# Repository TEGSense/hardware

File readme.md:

# TEG Sense Board

This is a thermoelectric generator (TEG) boost converter used to power a connected battery or capacitor to periodically operate a microcontroller reading from a biometric sensor to compute blood oxygen saturation. That was a big sentence!

This is the board version used in the published paper, revision 3 of the rigid prototypes.
It is used in conjunction with the [SpO2 board](https://github.com/TEGSense/hardware-spo2).
The board has a few bugs, so it's recommended to start with the [flex version](https://github.com/TEGSense/hardware-flex), even if you're not going to use a flex PCB.

## License

Shield: [![CC BY-SA 4.0][cc-by-sa-shield]][cc-by-sa]

This work is licensed under a
[Creative Commons Attribution-ShareAlike 4.0 International License][cc-by-sa].

[![CC BY-SA 4.0][cc-by-sa-image]][cc-by-sa]

[cc-by-sa]: http://creativecommons.org/licenses/by-sa/4.0/
[cc-by-sa-image]: https://licensebuttons.net/l/by-sa/4.0/88x31.png
[cc-by-sa-shield]: https://img.shields.io/badge/License-CC%20BY--SA%204.0-lightgrey.svg

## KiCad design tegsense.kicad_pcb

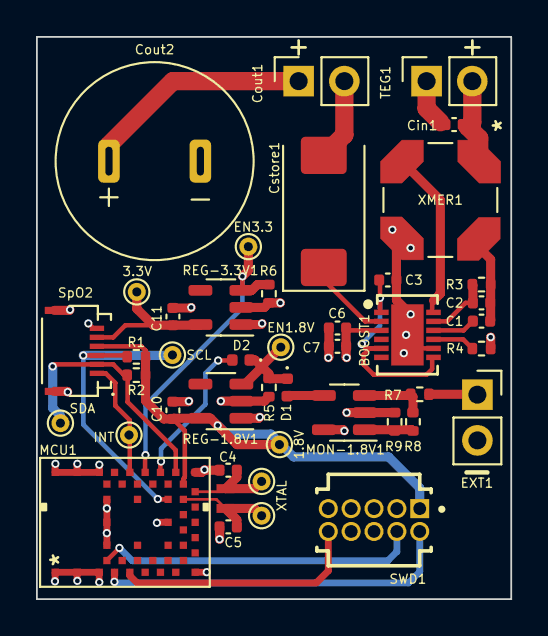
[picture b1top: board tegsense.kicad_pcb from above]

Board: 4 copper layers, 26.4 x 31.2 mm, 43 parts (0 on the bottom side), 26 nets.

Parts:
BOOST1: LTC3108IDEPBF; DFN-12_DE
C1: 1nF; C_0402_1005Metric
C2: 300pF; C_0402_1005Metric
C3, C6: 1uF; C_0402_1005Metric
C4, C5: 12pF; C_0402_1005Metric
C7, C10, C11: 2.2uF; C_0402_1005Metric
Cin1: 22uF; C_0402_1005Metric
Cout1: VAR; PinSocket_1x02_P2.54mm_Vertical
Cout2: VAR; KEMET_FY_Supercap
Cstore1: 330u; CP_EIA-7343-31_Kemet-D
D1, D2: 0.25V; D_0402_1005Metric
EXT1: Conn_01x02; PinSocket_1x02_P2.54mm_Vertical
MCU1: uC BMD-350-A-R; BMD-350-A-R
MON-1.8V1: MIC2779L; SOT-23-5
R1, R2: 2k; R_0402_1005Metric
R3: 499k; R_0402_1005Metric
R4: 10k; R_0402_1005Metric
R5, R6: 3M; R_0402_1005Metric
R7: 620k; R_0402_1005Metric
R8: 66.5k; R_0402_1005Metric
R9: 309k; R_0402_1005Metric
REG-1.8V1: S-1318-1.8V; SOT-23-5
REG-3.3V1: S-1318-3.3V; SOT-23-5
SWD1: Conn_ARM_JTAG_SWD_10; SAMTEC_FTSH-105-01-F-D-K
SpO2: 2328702-6; TE_2328702-6
TEG1: TEG; PinSocket_1x02_P2.54mm_Vertical
TP1: 1.8V; TestPoint_THTPad_D1.0mm_Drill0.5mm
TP2: INT; TestPoint_THTPad_D1.0mm_Drill0.5mm
TP3: EN1.8V; TestPoint_THTPad_D1.0mm_Drill0.5mm
TP4: EN3.3; TestPoint_THTPad_D1.0mm_Drill0.5mm
TP5: 3.3V; TestPoint_THTPad_D1.0mm_Drill0.5mm
TP6: SCL; TestPoint_THTPad_D1.0mm_Drill0.5mm
TP7: SDA; TestPoint_THTPad_D1.0mm_Drill0.5mm
TP8: XTAL; TestPoint_THTPad_2x_D1.0mm_Drill0.5mm
XMER1: LPR6235-752SMLC
Y1: XTAL; XTAL_ECS-.327-9-16-TR

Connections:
1.8V: C10.1, MCU1.25 (VCC), R1.1, R2.1, REG-1.8V1.5 (Vout), SWD1.1 (VTref), SpO2.4, TP1.1
3.3V: C11.1, REG-3.3V1.5 (Vout), SpO2.5, TP5.1
EN_1.8V: D1.2 (A), MON-1.8V1.4 (/RST)
GND: BOOST1.8 (VS1), BOOST1.13 (GND), C3.2, C4.1, C5.1, C6.1, C7.2, C10.2, C11.2, Cin1.2, Cout1.2, Cout2.2, Cstore1.2, EXT1.2, MCU1.1 (GND), MCU1.2 (GND), MCU1.3 (GND), MCU1.15 (GND), MCU1.26 (GND), MCU1.37 (GND), MCU1.38 (GND), MCU1.39 (GND), MCU1.40 (GND), MCU1.43 (GND), MCU1.46 (GND), MCU1.47 (GND), MON-1.8V1.2 (GND), R5.2, R6.2, R9.2, REG-1.8V1.2 (Vss), REG-3.3V1.2 (Vss), SWD1.3 (GND), SWD1.5 (GND), SWD1.9 (GNDDetect), SpO2.6, SpO2.S1 (SHIELD), SpO2.S2 (SHIELD), TEG1.1, XMER1.3
MCU_EN_1.8V: D2.2 (A), MCU1.29 (P0-30)
MCU_EN_3.3V: MCU1.31 (P0-29), R6.1, REG-3.3V1.3 (EN), TP4.1
unnamed: BOOST1.12 (SW), XMER1.2
unnamed: C1.1, C2.1, R3.1, XMER1.4
unnamed: BOOST1.10 (C1), C1.2
unnamed: BOOST1.11 (C2), C2.2, R3.2
unnamed: C4.2, MCU1.24 (P0-00/XTAL1), TP8.2, Y1.2
unnamed: C5.2, MCU1.23 (P0-01/XTAL2), TP8.1, Y1.1
unnamed: Cin1.1, TEG1.2, XMER1.1
unnamed: BOOST1.2 (Vstore), Cstore1.1
unnamed: D1.1 (K), D2.1 (K), R5.1, REG-1.8V1.3 (EN), TP3.1
unnamed: BOOST1.9 (Vout2_EN), R4.2
unnamed: MON-1.8V1.3 (LTH), R7.2, R8.1
unnamed: MON-1.8V1.1 (HTH), R8.2, R9.1
SCL: MCU1.44 (P0-03), R1.2, SpO2.3, TP6.1
SDA: MCU1.27 (P0-04), R2.2, SpO2.2, TP7.1
SENS_INT: MCU1.33 (P0-25), SpO2.1, TP2.1
SWDCLK: MCU1.4 (SWCLK), SWD1.4 (SWDCLK/TCK)
SWDIO: MCU1.5 (SWDIO), SWD1.2 (SWDIO/TMS)
VAUX: BOOST1.1 (VAUX), BOOST1.5 (Vldo), BOOST1.7 (VS2), C3.1
Vout: BOOST1.3 (Vout), C6.2, C7.1, Cout1.1, Cout2.1, EXT1.1, MON-1.8V1.5 (Vdd), R4.1, R7.1, REG-1.8V1.1 (Vin), REG-3.3V1.1 (Vin)
nRESET: MCU1.7 (P0-21/N_RESET), SWD1.10 (~RESET)

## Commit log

2024-06-28 Initial
2024-06-28 Updated to clarify board deprecation.
